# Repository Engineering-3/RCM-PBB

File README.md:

# RCM-PBB

RCM Power Buss Board

This is a power distribution board to be used independently or with the RCM Control Stack. The RCM-PBB is designed to supply a regulated 9V to each of the five outputs from a higher voltage battery. It features Anderson PowerPole battery connectors and a SPST on-off switch. Please see [Engineering3](http://engineering3.org/) for more information on the complete RCM Control Stack project.

Repository Contents
-------------------

* **/RCM-PBB_v1** Eagle schematic/board files, BOM, gerbers

Version History
---------------
* [RCM-PBB_v1](https://github.com/Engineering-3/RCM-PBB/tree/master/RCM-PBB_v1) - First public version - version 1 

License Information
-------------------
Hardware is released under [Solderpad Hardware License v0.51](http://solderpad.org/licenses/SHL-0.51/).
Distributed as-is; no warranty is given.

Getting Started Help
--------------------
This is a Plug-n-Play board.

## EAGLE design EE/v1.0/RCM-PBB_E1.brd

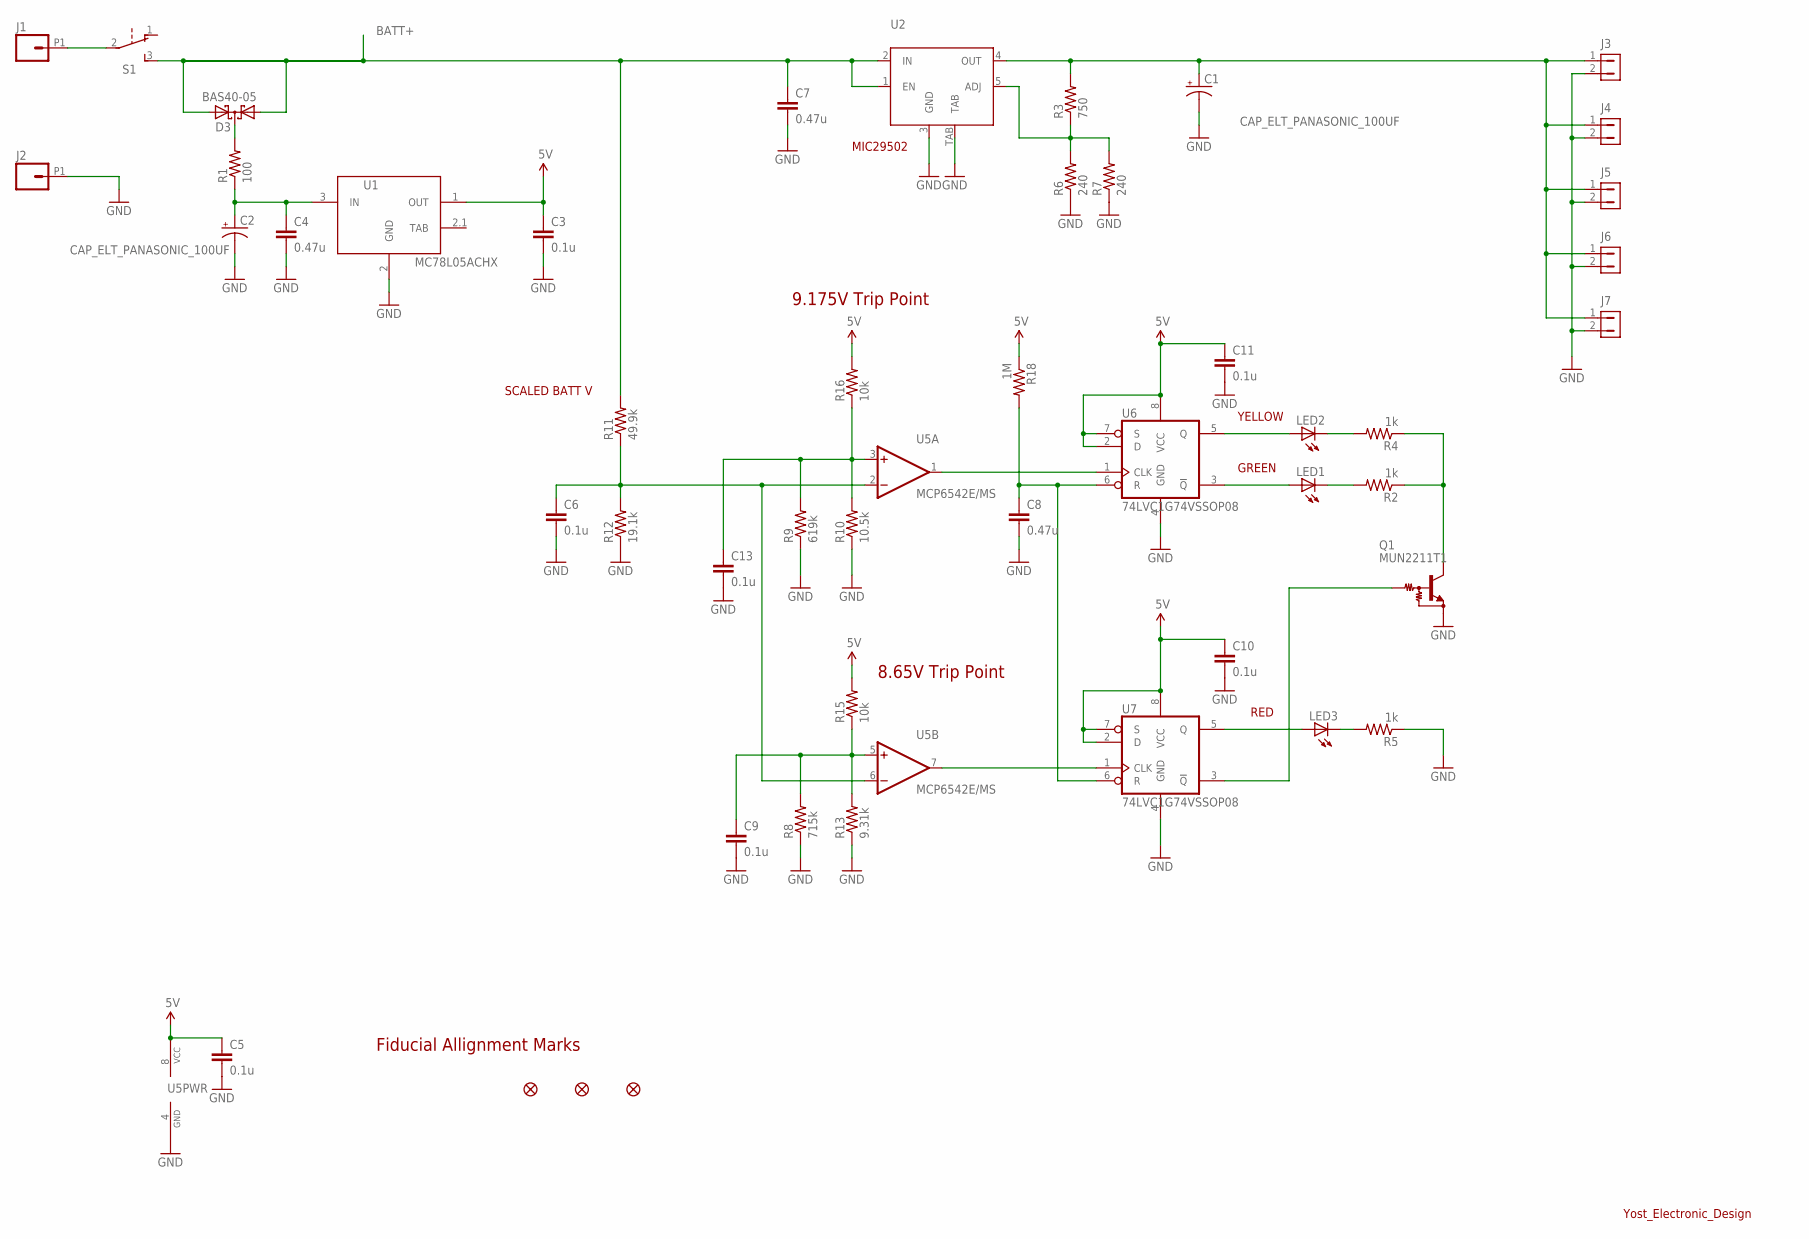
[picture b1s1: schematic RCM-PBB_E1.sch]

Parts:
C1, C2: CAP_ELT_PANASONIC_100UF; PANASONIC-D8-ELT-CAP
C3, C5, C6, C9, C10, C11, C13: 0.1u; 0805
C4, C7, C8: 0.47u; 0805
D3: BAS40-05; SOT23
J1, J2: ANDERSON_POWER_POLE
J3, J4, J5, J6, J7: CON1X2_SHROUDED; HEADER_1X2_SHROUDED
JP4, JP5, JP6: FIDUCIAL1X2.5; FIDUCIAL-1X2.5
LED1, LED2, LED3: LEDCHIPLED_0805; CHIPLED_0805
Q1: MUN2211T1; SC59-BEC
R1: 100; 0805
R2, R4, R5: 1k; 0805
R3: 750; 0805
R6, R7: 240; 0805
R8: 715k; 0805
R9: 619k; 0805
R10: 10.5k; 0805
R11: 49.9k; 0805
R12: 19.1k; 0805
R13: 9.31k; 0805
R15, R16: 10k; 0805
R18: 1M; 0805
S1: SWITCH_SLIDE_ON_ON; SWITCH_SLIDE_RA
U1: MC78L05ACHX; SOT89
U2: MIC29502WU; TO263-5
U5: MCP6542E/MS; MSOP8NOPAD
U6, U7: 74LVC1G74VSSOP08; VSSOP08

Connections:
5V: C3.1, C5.1, C10.1, C11.1, R15.2, R16.2, R18.1, U1.1 (OUT), U5.8 (VCC), U6.2 (D), U6.7 (S), U6.8 (VCC), U7.2 (D), U7.7 (S), U7.8 (VCC)
BATT+: C7.1, D3.1 (A1), D3.2 (A2), R11.2, S1.3 (S), U2.1 (EN), U2.2 (IN)
GND: C1.-, C2.-, C3.2, C4.2, C5.2, C6.2, C7.2, C8.2, C9.2, C10.2, C11.2, C13.2, J2.P1, J3.2, J4.2, J5.2, J6.2, J7.2, Q1.E, R5.1, R6.1, R7.1, R8.1, R9.1, R10.1, R12.1, R13.1, U1.2 (GND), U2.3 (GND), U2.TAB, U5.4 (GND), U6.4 (GND), U7.4 (GND)
unnamed: D3.3 (C), R1.2
unnamed: C13.1, R9.2, R10.2, R16.1, U5.3 (+IN)
unnamed: LED1.C, R2.2
unnamed: U5.1 (OUT), U6.1 (CLK)
unnamed: C8.1, R18.2, U6.6 (R), U7.6 (R)
unnamed: U5.7 (OUT), U7.1 (CLK)
unnamed: Q1.C, R2.1, R4.1
unnamed: C1.+, J3.1, J4.1, J5.1, J6.1, J7.1, R3.2, U2.4 (OUT)
unnamed: LED3.A, U7.5 (Q)
unnamed: J1.P1, S1.2
unnamed: LED1.A, U6.3 (!Q)
unnamed: C9.1, R8.2, R13.2, R15.1, U5.5 (+IN)
unnamed: LED3.C, R5.2
unnamed: C6.1, R11.1, R12.2, U5.2 (-IN), U5.6 (-IN)
unnamed: C2.+, C4.1, R1.1, U1.3 (IN)
unnamed: LED2.C, R4.2
unnamed: LED2.A, U6.5 (Q)
unnamed: Q1.B, U7.3 (!Q)
unnamed: R3.1, R6.2, R7.2, U2.5 (ADJ)

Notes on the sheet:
Yost_Electronic_Design
SCALED BATT V
GREEN
RED
YELLOW
8.65V Trip Point
Fiducial Allignment Marks
9.175V Trip Point
MIC29502

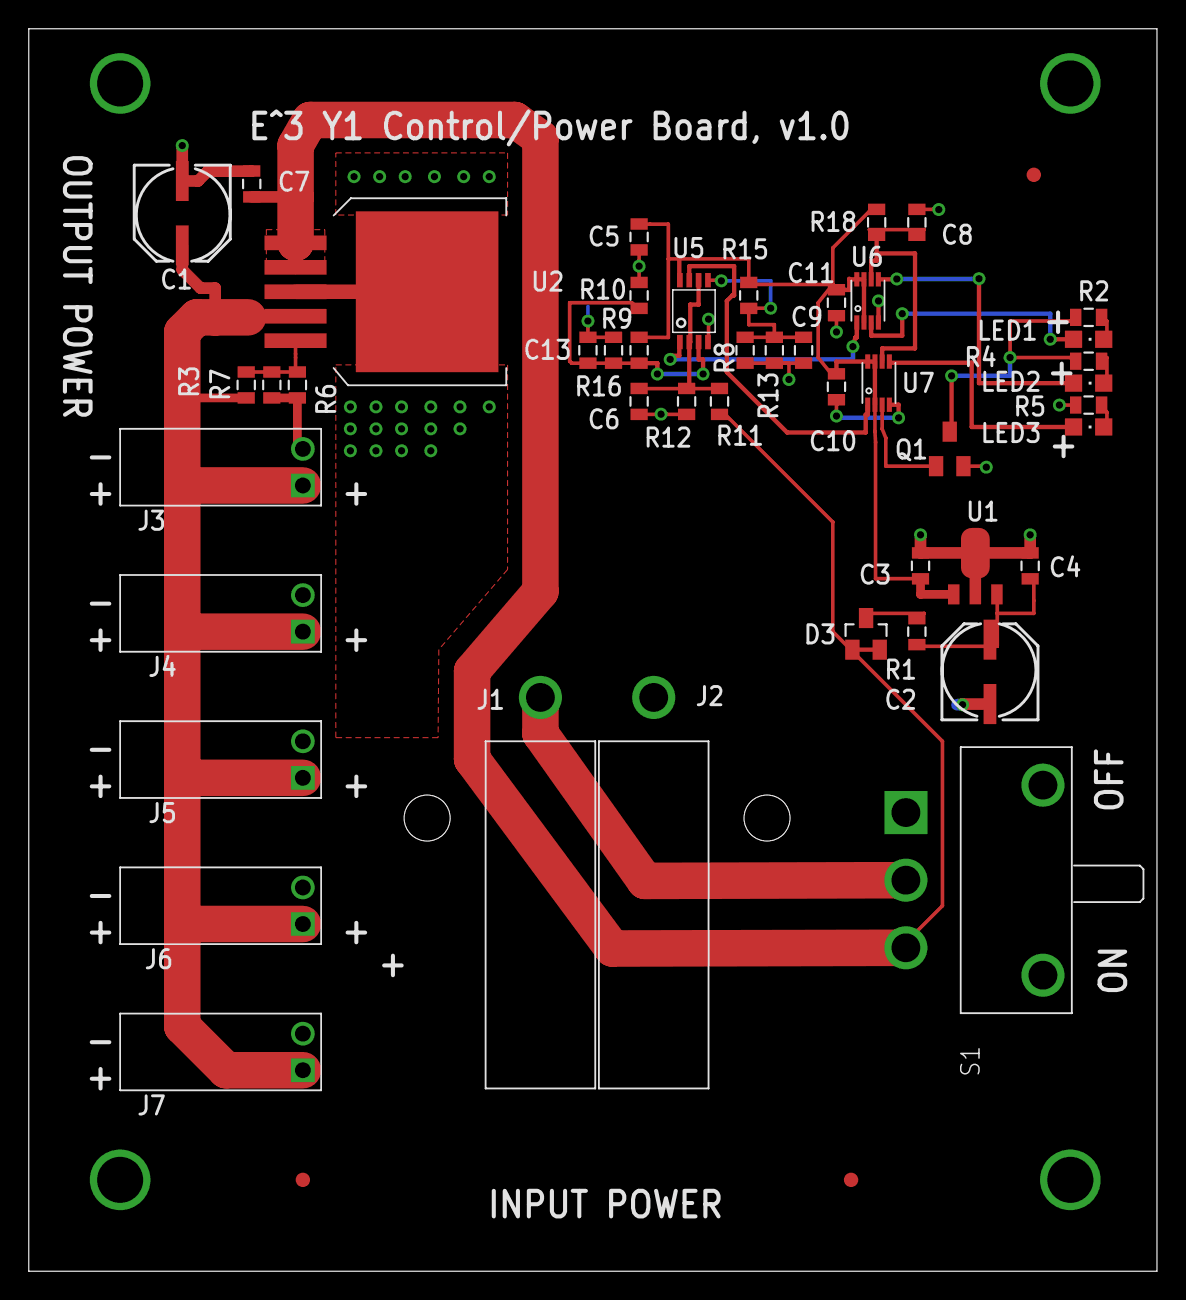
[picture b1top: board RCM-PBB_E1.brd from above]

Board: 2 copper layers, 78.4 x 86.3 mm, 49 parts (0 on the bottom side), 22 nets.

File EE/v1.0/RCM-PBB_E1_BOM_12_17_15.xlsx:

Reference Designator | Value | MFR | MFR Part Number | Digikey Part Number | Qty | Notes | 10-Price | 10-Qty | 10-Total | 100-Price | 100-Qty | 100-Total
C3,5,6,9,10,11,13 | 0.1u | Murata | GRM21BR71E104KA01L | 490-1673-1-ND | 7 | CAP0805 |  | 70 |  |  | 735
C1,2 | 100UF | Panasonic | EEE-1VA101XP | PCE3951CT-ND | 2 | CAP ALUM 100UF 35V 20% SMD D8-ELT-CAP |  | 20 |  |  | 210
C4,7,8 | 0.47u | Murata | C0805C474K3RACTU | 399-8098-1-ND | 3 | CAP CER .47UF 25V 10% X7R 0805 |  | 30 |  |  | 315
D3 | BAS40-05 | Diodes Inc | BAS40-05-7-F | BAS40-05-FDICT-ND | 1 | DIODE SCHTKY 350MW 40V SOT23-3 |  | 10 |  |  | 105
J1 | RED Housing | Anderson Power | 1327 | 879-1327 | 1 | ANDERSON_POWER_POLE RED |  | 10 |  |  | 105
J2 | BLACK Housing | Anderson Power | 1327G6 | 879-1327G6 | 1 | ANDERSON_POWER_POLE BLACK |  | 10 |  |  | 105
J1,2 | Blue Wings | Anderson Power | 1399G8-BK | 879-1399G8-BK | 2 | ANDERSON_POWER_POLE BLUE WINGS |  | 20 |  |  | 210
J1,2 | 25Amp Pins | Anderson Power | 1317G3 | 879-1377G4-BK | 2 | ANDERSON_POWER_25A STRAIGHT PINS |  | 20 |  |  | 210
J3,4,5,6,7 | CON1X2_SHROUDED | Molex | 70553-0036 | WM4924-ND | 5 | CONN HDR RT ANG 2POS .100 TIN |  | 50 |  |  | 525
LED3 | Red | Lite-On Inc | LTST-C171CKT | 160-1421-1-ND | 1 | LED ALGAAS RED THIN 0805 SMD |  | 10 |  |  | 105
LED1 | Green | Lite-On Inc | LTST-C171GKT | 160-1423-1-ND | 1 | LED GREEN CLEAR THIN 0805 SMD |  | 10 |  |  | 105
LED2 | Yellow | Lite-On Inc | LTST-C171YKT | 160-1431-1-ND | 1 | LED YELLOW CLEAR THIN 0805 SMD |  | 10 |  |  | 105
Q1 | MUN2211T1 | ON Semiconductor | MUN2211T1G | MUN2211T1GOSCT-ND | 1 | TRANS BRT NPN 100MA 50V SC59 |  | 10 |  |  | 105
R1 | 100 | Rohm Semiconductor | MCR10ERTF1000 | RHM100CHCT-ND | 1 | RES SMD 100 OHM 1% 1/8W 0805 |  | 10 |  |  | 105
R3 | 750 | Rohm Semiconductor | MCR10ERTF7500 | RHM750CHCT-ND | 1 | RES SMD 750 OHM 1% 1/8W 0805 |  | 10 |  |  | 105
R2,4,5 | 1k | Rohm Semiconductor | MCR10ERTF1001 | RHM1.00KCHCT-ND | 3 | RES SMD 1k OHM 1% 1/8W 0805 |  | 30 |  |  | 315
R6,7 | 240 | Rohm Semiconductor | MCR10ERTF2400 | RHM240CHCT-ND | 2 | RES SMD 240 OHM 1% 1/8W 0805 |  | 20 |  |  | 210
R8 | 715k | Rohm Semiconductor | MCR10ERTF7153 | RHM715KCHCT-ND | 1 | RES SMD 715K OHM 1% 1/8W 0805 |  | 10 |  |  | 105
R9 | 619k | Rohm Semiconductor | MCR10ERTF6193 | RHM619KCHCT-ND | 1 | RES SMD 619K OHM 1% 1/8W 0805 |  | 10 |  |  | 105
R15,16 | 10k | Rohm Semiconductor | MCR10ERTF1002 | RHM10.0KCHCT-ND | 2 | RES SMD 10K OHM 1% 1/8W 0805 |  | 20 |  |  | 210
R11 | 49.9k | Rohm Semiconductor | MCR10ERTF4992 | RHM49.9KCHCT-ND | 1 | RES SMD 49.9K OHM 1% 1/8W 0805 |  | 10 |  |  | 105
R12 | 19.1k | Rohm Semiconductor | MCR10ERTF1912 | RHM19.1KCHCT-ND | 1 | RES SMD 19.1K OHM 1% 1/8W 0805 |  | 10 |  |  | 105
R13 | 9.31k | Rohm Semiconductor | MCR10ERTF9311 | RHM9.31KCHCT-ND | 1 | RES SMD 9.31K OHM 1% 1/8W 0805 |  | 10 |  |  | 105
R10 | 10.5k | Rohm Semiconductor | MCR10ERTF1052 | RHM10.5KCHCT-ND | 1 | RES SMD 10.5K OHM 1% 1/8W 0805 |  | 10 |  |  | 105
R18 | 1M | Rohm Semiconductor | MCR10EZPF1004 | RHM1.00MCRCT-ND | 1 | RES 1.00M OHM 1/8W 1% 0805 SMD |  | 10 |  |  | 105
S1 | SWITCH_SLIDE_ON_ON | E-Switch | 500SSP1S1M6QEA | EG2478-ND | 1 | SWITCH SLIDE SPDT SILVR 5A RTANG |  | 10 |  |  | 105
U1 | MC78L05ACHX | Fairchild Semiconductor | MC78L05ACHX | MC78L05ACHXCT-ND | 1 | IC VREG 100MA 5V SOT-89 |  | 10 |  |  | 105
U5 | MCP6542E/MS | Micro Chip Technology | MCP6542-E/MS | MCP6542-E/MS-ND | 1 | IC COMP 1.6V DUAL P-P 8MSOP |  | 10 |  |  | 105
U6,7 | 74LV1G74 | NXP Semiconductors | 74LVC1G74DC,125 | 568-4494-1-ND | 2 | IC SNGL D FF POS-EDG TRIG 8VSSOP |  | 20 |  |  | 210
U2 | MIC29502 | Micrel | MIC29502WU | 576-1146-1-ND | 1 | IC REG LDO ADJ 5A TO263-5 |  | 10 |  |  | 105
PCB |  | Xtreme | EN3-RCM-PBB-PCB+E1 | EN3-RCM-PBB-PCB+E1 | 1 | EN3-RCM-PBB-PCB+E1 |  | 8 |  |  | 100

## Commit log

2016-07-27 Initial check in of E1 version of Power Buss Board. Includes v1 and v2 versions of the board.
2016-07-28 Renaming some files for v1.0, and adding BOM Excel file.
2016-07-28 Fixed minor error in BOM.
2016-07-28 Fixed another minor error in the BOM, updated filenames.
2016-08-01 Added board build readme.
2018-09-29 Added alternate 5V LDO for U1.

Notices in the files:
parts and their libraries:
SparkFun-Aesthetics: Licensing: CC v3.0 Share-Alike You are welcome to use this library for commercial purposes.
